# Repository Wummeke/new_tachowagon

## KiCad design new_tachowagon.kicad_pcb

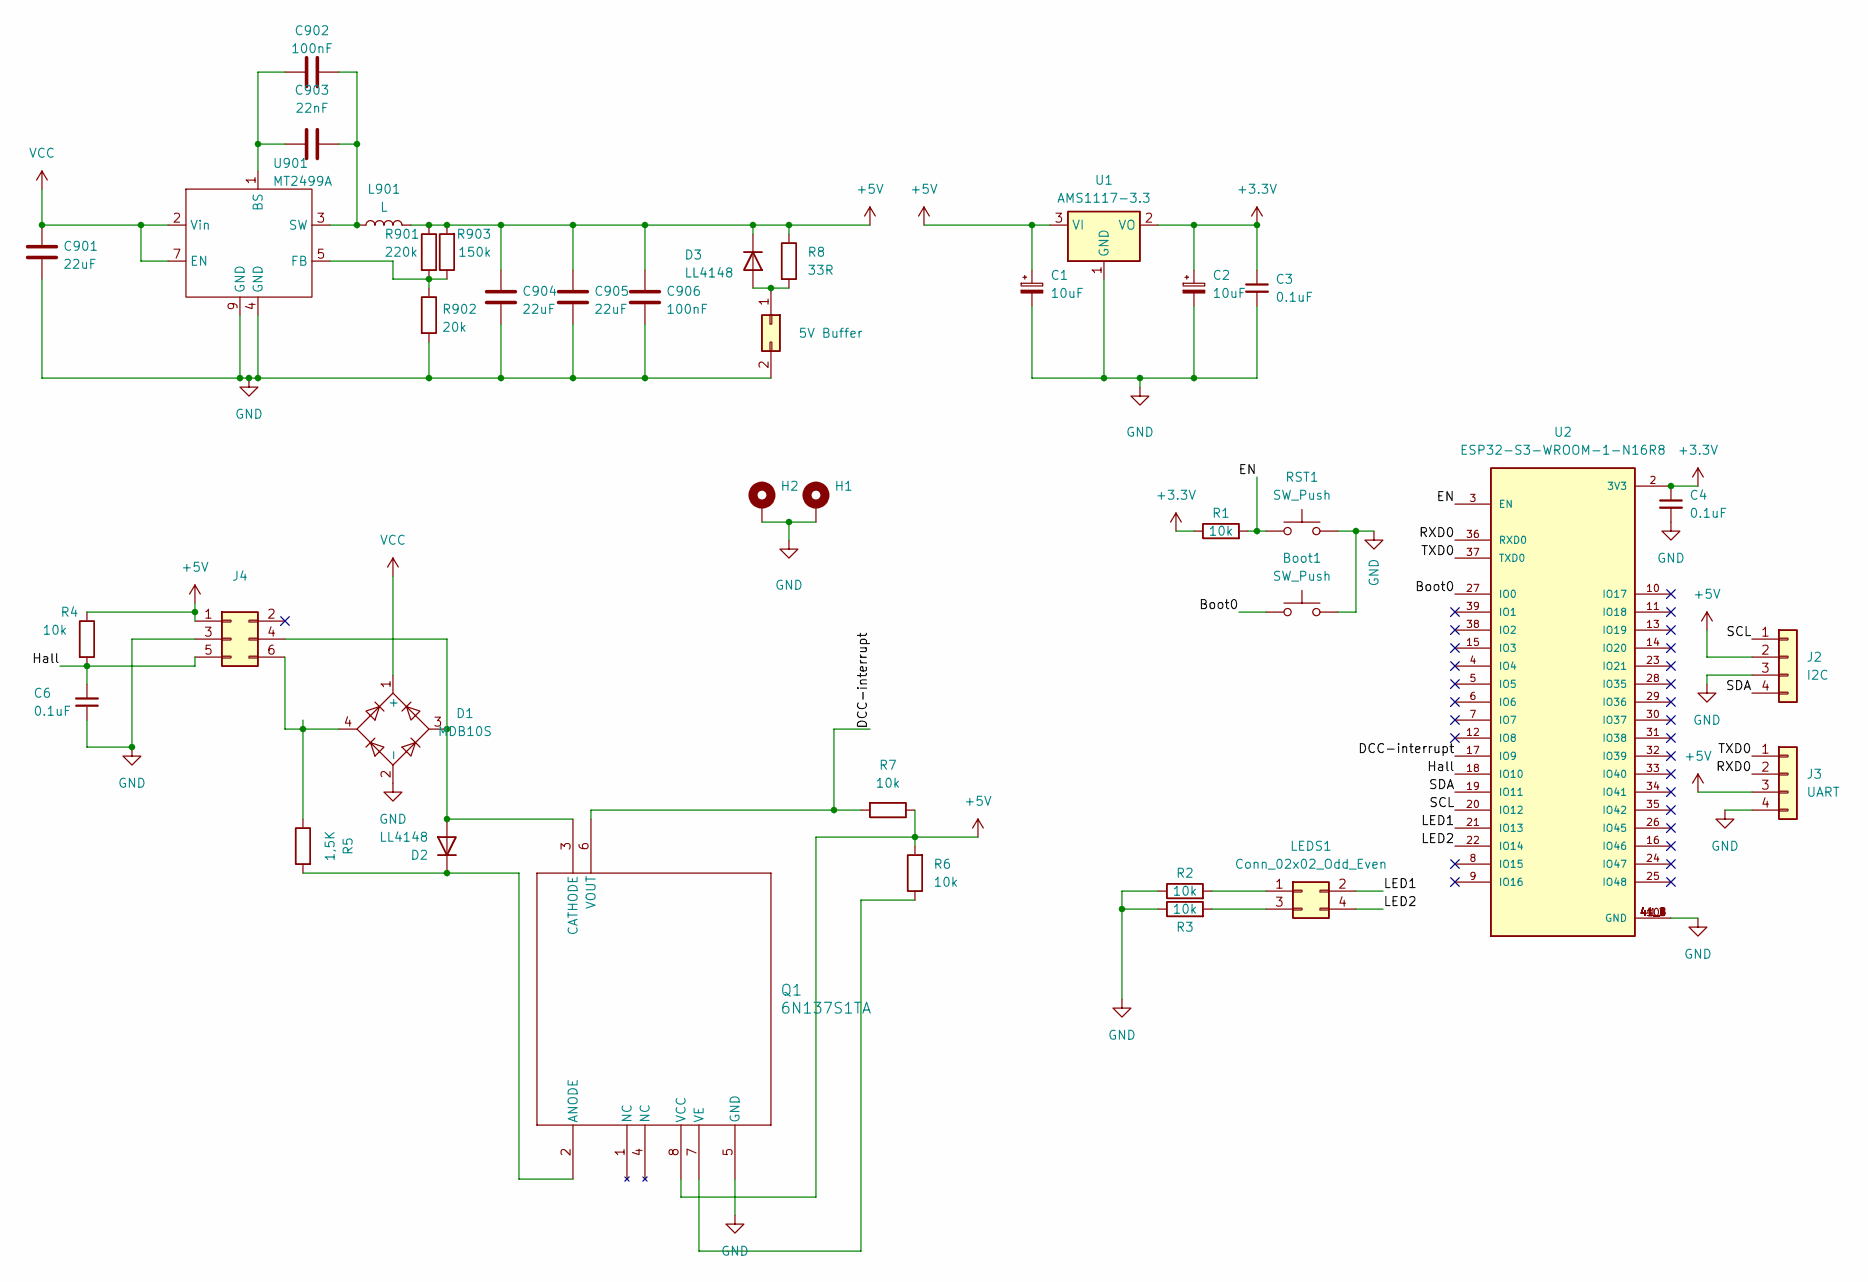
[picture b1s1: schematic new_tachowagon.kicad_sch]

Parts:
Boot1: SW_Push; SW_Push_1P1T_XKB_TS-1187A; LCSC C318884
C1, C2: 10uF; C_0603_1608Metric; JLCPCB Part# C96446
C3, C4, C6: 0.1uF; C_0603_1608Metric; JLCPCB Part# C14663
C901, C904, C905: 22uF; C_0603_1608Metric; JLCPCB Part# C45783
C902, C906: 100nF; C_0402_1005Metric; JLCPCB Part# C307331
C903: 22nF; C_0402_1005Metric; JLCPCB Part# C1532
D1: MDB10S; SOIC245P670X290-4N; LCSC C2488
D2, D3: LL4148; D_SOD-123; JLCPCB Part# C81598
H1, H2: MountingHole_Pad; MountingHole_3.2mm_M3_DIN965_Pad
J1: 5V Buffer; PinHeader_2x01_P2.54mm_Vertical
J2: I2C; PinHeader_1x04_P2.54mm_Vertical
J3: UART; PinHeader_1x04_P2.54mm_Vertical
J4: Conn_02x03_Odd_Even; PinHeader_2x03_P2.54mm_Vertical
L901: L; L_Bourns-SRN8040_8x8.15mm; JLCPCB Part# C92945
LEDS1: Conn_02x02_Odd_Even; PinHeader_2x02_P2.54mm_Vertical
Q1: 6N137S1TA; 6N137S1TA_EVE; LCSC C110020
R1, R2, R3, R4, R6, R7: 10k; R_1206_3216Metric; JLCPCB Part# C17902
R5: 1,5K; R_0805_2012Metric; JLCPCB Part# C4310
R8: 33R; R_2512_6332Metric_Pad1.40x3.35mm_HandSolder
R901: 220k; R_0603_1608Metric; JLCPCB Part# C22961
R902: 20k; R_0603_1608Metric; JLCPCB Part# C4328
R903: 150k; R_0603_1608Metric; JLCPCB Part# C22807
RST1: SW_Push; SW_Push_1P1T_XKB_TS-1187A; LCSC C318884
U1: AMS1117-3.3; SOT-223-3_TabPin2; LCSC C6186
U2: ESP32-S3-WROOM-1-N16R8; XCVR_ESP32-S3-WROOM-1-N16R8
U901: MT2499A; TI_SO-PowerPAD-8; JLCPCB Part# C3007555

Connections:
+3.3V: C2.1, C3.1, C4.1, R1.1, U1.2 (VO), U2.2 (3V3)
+5V: C1.1, C904.1, C905.1, C906.1, D3.1 (K), J2.2, J3.3, J4.1, L901.2, Q1.8 (VCC), R4.1, R6.2, R7.1, R8.1, R901.1, R903.2, U1.3 (VI)
/Boot0: Boot1.1, U2.27 (IO0)
/DCC-interrupt: Q1.6 (VOUT), R7.2, U2.17 (IO9)
/EN: R1.2, RST1.1, U2.3 (EN)
/Hall: C6.2, J4.5, R4.2, U2.18 (IO10)
/LED1: LEDS1.2, U2.21 (IO13)
/LED2: LEDS1.4, U2.22 (IO14)
/RXD0: J3.2, U2.36 (RXD0)
/SCL: J2.1, U2.20 (IO12)
/SDA: J2.4, U2.19 (IO11)
/TXD0: J3.1, U2.37 (TXD0)
GND: Boot1.2, C1.2, C2.2, C3.2, C4.2, C6.1, C901.2, C904.2, C905.2, C906.2, D1.2 (-), H1.1, H2.1, J1.2, J2.3, J3.4, J4.3, Q1.5 (GND), R2.1, R3.1, R902.2, RST1.2, U1.1 (GND), U2.1 (GND), U2.40 (GND), U2.41_1 (GND), U2.41_2 (GND), U2.41_3 (GND), U2.41_4 (GND), U2.41_5 (GND), U2.41_6 (GND), U2.41_7 (GND), U2.41_8 (GND), U2.41_9 (GND), U901.4 (GND), U901.9 (GND)
unnamed: D1.3, D2.2 (A), J4.4, Q1.3 (CATHODE)
unnamed: D2.1 (K), Q1.2 (ANODE), R5.2
unnamed: D3.2 (A), J1.1, R8.2
unnamed: D1.4, J4.6, R5.1
unnamed: LEDS1.1, R2.2
unnamed: LEDS1.3, R3.2
unnamed: Q1.7 (VE), R6.1
unnamed: C902.1, C903.1, U901.1 (BS)
unnamed: R901.2, R902.1, R903.1, U901.5 (FB)
unnamed: C902.2, C903.2, L901.1, U901.3 (SW)
VCC: C901.1, D1.1 (+), U901.2 (Vin), U901.7 (EN)

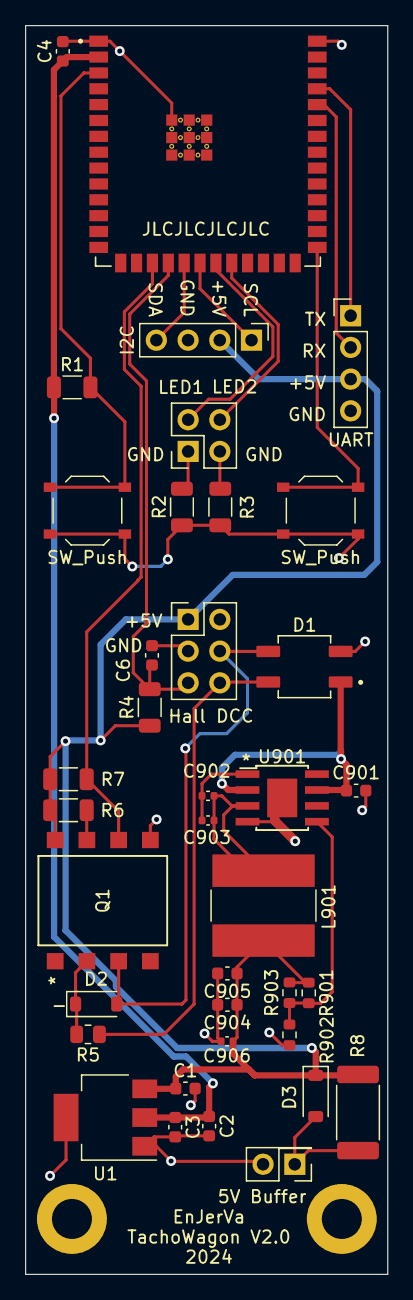
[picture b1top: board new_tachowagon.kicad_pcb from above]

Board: 2 copper layers, 29.0 x 100.0 mm, 39 parts (0 on the bottom side), 24 nets.

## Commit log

2024-08-09 added hierachic sheets
